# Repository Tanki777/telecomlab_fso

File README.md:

# Modulation Schemes for Free Space Optical Communication
This repository contains all GNU Radio flowgraphs, Matlab and python scripts that were used during the project. Additionally, the test data which was transmitted and received during the experiments, as well as a documentation are included.

## Table of contents
1. [GNU Radio flowgraphs](#1-gnu-radio-flowgraphs)
2. [Matlab scripts](#2-matlab-scripts)
3. [Utility scripts](#3-utility-scripts)
4. [Electrical](#4-electrical)
5. [Troubleshooting](#5-troubleshooting)

## 1. GNU Radio flowgraphs
If you are new to GNU Radio, it is recommended to have a look at the official [tutorials](https://wiki.gnuradio.org/index.php/Tutorials) first. After that, the following descriptions will be easier to understand.  
While reading the following descriptions, it is adviced to open the corresponding flowgraph image to follow the explanations.  
For this project, GNU Radio 3.10.12 was used.

### 1.1 Phase Shift Keying

#### 1.1.1 Random source transmission
This section refers to the flowgraphs ``ber_bpsk.grc``, ``ber_qpsk.grc``, ``ber_8psk.grc`` and ``ber_16psk.grc``. The diagram images can be found here: [ber_bpsk.pdf](GNU_Radio/Images/ber_bpsk.pdf), [ber_qpsk.pdf](GNU_Radio/Images/ber_qpsk.pdf), [ber_8psk.pdf](GNU_Radio/Images/ber_8psk.pdf), [ber_16psk.pdf](GNU_Radio/Images/ber_16psk.pdf).

The flowgraphs transmit a random source, which are bytes with values between 0 and 255. A random sequence of 30,000 bytes is sent and repeated while the flowgraph is running.

The transmission data is then modulated with the generic ``Constellation Modulator`` block, which can take different ``Constellation Object`` blocks as input. The ``Constellation Modulator`` also applies a Root-raised cosine filter. Since differential encoding is used, the constellation type parameter of the ``Constellation Object`` must not be set to ``QPSK`` as that prevents differential encoding and will not work. Instead, ``DQPSK`` may be selected. However, it is recommended to not use the preset types and instead set it to ``Variable Constellation`` and define symbol mapping and constellation points manually.

After that, the modulated signal is sent to the Pluto SDR (configured as the transmitter) using the ``PlutoSDR Sink`` block via USB and received at the Pluto SDR (Configured as the receiver), which sends the signal back to the computer via USB using the ``PlutoSDR Source`` block. In this project, two SDRs were used (one as transmitter, one as receiver). Thus, the IP in the Pluto blocks must be set accordingly in the ``IIO context URI`` parameter.

A ``FFT Root Raised Cosine Filter`` block is needed to match the filter at the transmitter.

In the ``Symbol Sync`` block, the symbols are synchronized. Different algorithms in the ``Timing Error Detector`` can be tested, while in our project y[n]y'[n] Maximum likelihood turned out to be the best overall.

The ``Costas Loop`` block locks the phase, making the constellation points appear as expected in the ``QT GUI Constellation Sink`` block. The ``Order`` parameter must be set according to how many constellation points are used. The exception is 16-PSK, where the order is still 8 (8 is the maximum value).

The ``Constellation Decoder`` block then decodes the complex signal to bytes.

Since differential encoding is used at the transmitter, a ``Differential Decoder`` block is required at the receiver.

The ``Map`` block remaps the symbol bytes and the order of the list must be the same as in the ``Constellation Object``.

Until now, the signal contains log~2~(p) bits per byte, where p is the number of constellation points. Therefore, it must be unpacked such that each byte contains one bit.

Finally, the data is written to the file as configured in the ``File Sink`` block.

The ``Probe Rate`` block regularly prints the bit rate to the terminal.

#### 1.1.2 General File transmission
This section refers to the flowgraphs ``pluto_bpsk_tx/rx.grc``, ``pluto_qpsk_tx/rx.grc`` and ``pluto_8psk_tx/rx.grc``. The diagram images can be found here: [pluto_bpsk_tx.pdf](GNU_Radio/Images/pluto_bpsk_tx.pdf), [pluto_bpsk_rx.pdf](GNU_Radio/Images/pluto_bpsk_rx.pdf), [pluto_qpsk_tx.pdf](GNU_Radio/Images/pluto_qpsk_tx.pdf), [pluto_qpsk_rx.pdf](GNU_Radio/Images/pluto_qpsk_rx.pdf), [pluto_8psk_tx.pdf](GNU_Radio/Images/pluto_8psk_tx.pdf), [pluto_8psk_rx.pdf](GNU_Radio/Images/pluto_8psk_rx.pdf).

These flowgraphs transmit any file, implementing the packeting inside the flowgraph. In contrast to repeated source transmission, the receiver should be turned on before the transmitter. Thus, the flowgraphs are splitted into a transmitter and receiver.  
A GNU Radio [tutorial](https://wiki.gnuradio.org/index.php?title=File_transfer_using_Packet_and_BPSK&oldid=14511)[^old_version] was used as a starting point (author: Dubbage) and modified.
The modulation scheme and the RB (Resource Blocks) used can be configured changing the value of ``txsim.RC``, to find the ``R.`` use the Wireless Waveform Generator Tool/App that in the "reference channel" dropdown shows the modulation scheme and Resource blocks used plus other info. Resource Blocks are important as they define the necessary bandwidth.

**Transmitter:**  
A HIER block ``File Source Packaged`` is used to read the file which should be transmitted and does the following (the diagram image can be found here: [hier_file_source_packaged.pdf](GNU_Radio/Images/hier_file_source_packaged.pdf)).

- It starts with an embedded python block ``EPB: File Source to Tagged Stream``, which first sends a preamble 64 times, then sends the file data in packets (each packet contains as many bytes as configured in the ``Pkt_len`` parameter of the ``File Source Packaged`` block). In front of each file data packet, the packet number is put. At the end, an end of file marker, the file name and a repeated post filler (64 times) is sent. A tag with the (new) packet length is also applied to make it a tagged stream (required by other blocks later). 
While the file data is encoded in Base64, everything else (including the packet number) is not encoded. The encoded file data packet is 4/3 as long as the decoded one, since Base64 encodes 3 Bytes into 4 Bytes.  
The **preamble** is ``&U...U]`` (50 times U), the **packet number frame** ``[000001]`` (always 6 digits, therefore a maximum of 999,999 packets are possible. This means a maximum file size of 999,999 times Pkt_len bytes. If larger files are desired, increase packet length or adjust packet number frame.), the **end of file marker** ``%UUU#EOF`` (followed by the file name), the **post filler** ``%UUU#EOF`` followed by 43 times the character ``U`` and ending with ``]``.
- After the embedded python block, a CRC32 code is also attached to each packet by the ``Stream CRC32`` block to detect errors at the receiver. The ``Mode`` parameter must be set to generate.
- Finally a header is also attached (including the access key ``11100001010110101110100010010011``) using the ``Protocol Formatter`` and ``Tagged Stream Mux`` blocks. The access key is used at the receiver for correlation.

As in random source transmission, the data is modulated by the ``Constellation Modulator`` block using a ``Constellation Object`` (which is configured depending on the number of constellation points). For more details, see the previous section.

The modulated signal is then sent to the Pluto SDR (configured as transmitter) using the ``PlutoSDR Sink`` via USB and sent to the Pluto SDR (configured as receiver).

**Receiver:**  
The received signal is sent to the computer via USB using the ``PlutoSDR Source`` block.

A ``FFT Root Raised Cosine Filter`` block is used to match the filter at the transmitter (which is inside of the ``Constellation Modulator`` block).

In the ``Symbol Sync`` block, the symbols are synchronized. Different algorithms in the ``Timing Error Detector`` can be tested, while in our project y[n]y'[n] Maximum likelihood turned out to be the best overall.

The ``Costas Loop`` block locks the phase, making the constellation points appear as expected in the ``QT GUI Constellation Sink`` block. The ``Order`` parameter must be set according to how many constellation points are used. The exception is 16-PSK, where the order is still 8 (8 is the maximum value).

The ``Constellation Decoder`` block then decodes the complex signal to bytes.

Since differential encoding is used at the transmitter, a ``Differential Decoder`` block is required at the receiver.

The ``Probe Rate`` block at this time does not print the bit rate, but the symbol rate (except for BPSK as it is the same there).

A HIER block ``File Sink Unpackaged mod_scheme`` is used to perform further actions before writing the data to a file. Since the mapping and unpacking depends on the constellation points, there is one block for each modulation scheme (the diagram images can be found here: [hier_file_sink_unpackaged_bpsk.pdf](GNU_Radio/Images/hier_file_sink_unpackaged_bpsk.pdf), [hier_file_sink_unpackaged_qpsk.pdf](GNU_Radio/Images/hier_file_sink_unpackaged_qpsk.pdf), [hier_file_sink_unpackaged_8psk.pdf](GNU_Radio/Images/hier_file_sink_unpackaged_8psk.pdf)).

- The ``Map`` block remaps the symbol bytes and the order of the list must be the same as in the ``Constellation Object`` (not needed in BPSK, since there is only 0 and 1).
- Until now, the signal contains log~2~(p) bits per byte, where p is the number of constellation points. Therefore, it must be unpacked such that each byte contains one bit (not needed in BPSK, since symbol is only 1 bit).
- The ``Correlate Access Code - Tag Stream`` block looks for the access code. If not found (with the ``Threshold`` parameter, the maximum number of wrong bits allowed can be changed), the packet will already be dropped at this point. The access code used is ``TODO``.
- The data is repacked from 1 relevant bit per byte (that is how the previous block outputs the data) to 8 relevant bits per byte (that is how the next block expects the data if ``Packed`` is true).
- The ``Stream CRC32`` is now set to ``Mode`` check. It drops packets when errors in the payload are detected.
- Finally, the data (without header and CRC32 checksum) is written to the configured file.

The ``File Sink Unpackaged mod_scheme`` block also outputs the input and output signal of the ``Correlate Access Code - Tag Stream`` block, comparing them in ``QT GUI Time Sink`` blocks. If, during transmission, there is an input signal but no output signal, the access code correlation failed and the packet is dropped. If there is no output signal visible during the entire transmission, it indicates something is wrong with the flowgraph.

#### 1.1.3 File transmission using pre-processed .bin files
This section refers to the flowgraphs ``raw_file_bpsk_tx/rx.grc`` and ``raw_file_qpsk_tx/rx.grc``. The diagram images can be found here: [raw_file_bpsk_tx.pdf](GNU_Radio/Images/raw_file_bpsk_tx.pdf), [raw_file_bpsk_rx.pdf](GNU_Radio/Images/raw_file_bpsk_rx.pdf), [raw_file_qpsk_tx.pdf](GNU_Radio/Images/raw_file_qpsk_tx.pdf), [raw_file_qpsk_rx.pdf](GNU_Radio/Images/raw_file_qpsk_rx.pdf).

### 1.2 Important notes using Pluto SDR
When testing flowgraphs and if the TX and RX SMA connectors of the SDRs are directly connected to each other with a cable, make sure to set the ``Attenuation TX1`` parameter of the ``PlutoSDR Sink`` block to **at least 20 dB** to prevent damaging the device. Only when using antennas or the laser, it can be set to 0 dB.

## 2. Matlab scripts

## 2.1 OFDM
To test the optical channel with more complex modulation schemes, a MATLAB help example (see https://it.mathworks.com/help/lte/ug/image-transmission-reception-using-lte-waveform-and-sdr.html for the original example) was adapted for the setup. This script encodes and packs an image into a radio frame. A baseband LTE signal with OFDM modulation is transmitted. The signal is then received, and the frequency offset is determined. After OFDM demodulation, a channel estimation is performed, and the payload of the received packets is recombined to form the received image.
OFDM subcarriers were modulated using 64-QAM (in the uploaded code, like in the original example), and 16-QAM. 

## 2.2 Pre-Processed Binary File Transmission
In the folder there are the Matlab codes used to create packets from the binary file generated from the image 'capra.jpg', 'transmit_packets.m', and to post-process the file after it has been received, 'read_received.m', that recreates the image. The folder 'transmitted_file' contains the packeted file, the folder 'received_files' contains the successfully received files, before post-processing.

## 3. Utility scripts

### 3.1 Post-processing for file transmission using GNU Radio flowgraph
If using one of the following flowgraphs ``pluto_bpsk_rx/tx.grc``, ``pluto_qpsk_rx/tx.grc`` or ``pluto_8psk_rx/tx.grc``, the received ``.tmp`` file must be post-processed to reconstruct the file data. For this, the script ``strip_preamble_mod.py`` can be used.  
The original script is authored by duggabe (see [here](https://wiki.gnuradio.org/index.php?title=File_transfer_using_Packet_and_BPSK&oldid=14511)) and was modified.[^old_version]

[^old_version]: Note that the GNU Radio tutorial was reworked and this link refers to the older version which was used in this project.

**Usage:**
````
python .\strip_preamble_mod.py in_file_name.tmp out_file_name.txt
````
The file extension of the output file must match that of the transmitted file.

**What it does:**
- Removes preamble.
- Looks for packet number frames.
- Decodes payload data (Base64) chunk-wise (each chunk is 4 Bytes) and writes it to the output file.
- Prints how many (and which) packet number frames were not detected.
- Compares content of detected packets with transmitted file and checks for bit errors.
- Prints packet error rate.

**Configuration:**  
Before using the script, it should be configured for the used transmission file and setting. The following should be checked and edited if necessary.
- Packet length (only if modified in the flowgraph).
- Preamble, end of file marker, post filler content (only if modified in the embedded python block in the flowgraph).
- Total number of packets for the transmitted file (is displayed in GNU Radio terminal after the transmission has ended).
- Whether the received file content should be compared with the transmitted file.
- Filename of the transmitted file (only if the received file content is compared with the transmitted file).

### 3.2 Missing number check for .txt files for file transmission using GNU Radio flowgraph
If using one of the flowgraphs listed in the previous section, the script ``txt_scanner.py`` can check which numbers are missing in the received file.

**Requirements:**
- The transmitted file contains ordered incrementing numbers (by 1), separated by commas (see ``test_file_tx.txt``).

**Usage:**

````
python .\txt_scanner.py
````

**What it does:**
- Prints how many (and which) numbers are missing in the received file.

**Configuration:**  
Before using the script, it should be configured as follows.
- Edit the name of the received file.
- Edit the list of numbers to be checked to match the transmitted file content.

# 4. Electrical
## 4.1 Electrical schematics
All the design files are available in the folder "ElectricalDesign", which is subdivided into "Version 1" and "Version 2". The first is the one used during our tests. The second is the improved version with all the problems we encountered fixed, plus some other nice features like pin names, use of rule areas, fixed voltage reference for the amplifier, but with the possibility to switch back to the DAC if needed, and monitor of the amplifier voltage directly from VBUS of INA226, while shunt voltage keeps reading the photodiode resistor voltage. Moreover pull-up resistors were added.
For the first version the 3 pins on the right of the receiver (SMA down) can't be used to set the voltage to the linear converter, if you want to do so remove first the DAC. Consider that SET pin provides a constant current, handle with care this connection! (Use a resistor) The central pin is a ground reference

## 4.2 Electrical connections
To connect the Arduino with the receiver you can simply connect grount to the lowermost pin (always SMA down), then moving up 5V, SDA, SCL as shown [here](ElectricalDesign/Version1/Pinout Receiver.png). On the Arduino side, if using an Arduino Mega 2560, use pin 20 for SDA and 21 for SCL. In case of Arduino Uno, connect SDA to A4 and SCL to A5, if using R4 version add pull-up resistors from the data lines to 5V or to 3.3V! You can connect 5V to Arduino's 5V pins and remember to always connect ground to the board and Arduino, even if using an external power supply.
Connect the SMA connector to the receiver port of your radio with a suitable cable.

To connect the transmitter use the given cable (D-SUB connectors), and connect it to the laser driver. The cable has a mark to indicate the transmitter (laser) side. If you want to use a desk power supply (only 1M OPV310!) connect the cable as described before, then add the cut cable and connector available in the box. On the wires cut there is a marking for "LS" Laser, "PD" Photodiode, and GND for Ground. Always use a multimeter in current mode to check the current that should never exceed 7mA. Connect the multimeter in series to the transmitter. DO NOT TRUST THE CURRENT READINGS OF THE POWER SUPPLY, might damage the laser and exceed the 1M cathegory.
Connect the SMA connector to the trasmitter port of the radio using a suitable connection

## 4.3 Alignment
To align the recevier you can run the program ``ADD LINK ARDUINO PROGRAM`` on the Arduino connected to the receiver while leaving only  ``INA.getShuntVoltage_uV();`` and its print not commented. Run the program and open the serial plotter, this will show the average voltage of the resistor connected to the photodiode, the more light enters the photodiode the greater the current it will let pass, the higher the voltage of the resistor will be. Start roughly aligning the transmitter and the receiver, you can help yourself with a phone camera, they usually seee in the NIR spectrum. after the rough alignment you can then check the serial plotter and try to reach the maximum value by moving both the receiver and transmitter set screws. Beware of local maxima, OPV302 has an output light concentration donut shaped, with the maximas on the outer part. Expect values around 1600uV for 6mA on the laser, with a receiver lens, and at oughly 1m, check the report for other values.
You can also calculate the current of the photodiode by dividing the voltage by 50, the resistance value of the resistor of the photodiode. with the current you could calculate the power that enters the photodiode, at 850nm you can divide the current by 0.3 to find the input power, check the datasheet for other wavelengths.

# 5. Troubleshooting

## 5.1 General

**Q:** Impossible to find DAC or ADC or setup is not successfu (error from the code).

**A:** Check that that the 2 wires of I2C are connected properly SDA->SDA SCL->SCL, check to have a ground connection between the Arduino and the receiver, in case you are using an external power supply. If this is ok then if you are using an Arduino Uno R4 you need external pullup resistors (from 2.2k to 20k connected to 5V or 3.3V). If you are using an Arduino Mega check which I2C pair you are using, there are many! If free always choose the first couple, located at pin 20 and 21. 
The schematics annotated of the first version are available [here](ElectricalDesign/Version1/Pinout Receiver.png), for the second version the pins are annotated in the silkscreen.

## 5.2 GNU Radio flowgraphs
**Q:** The signal is bad, what could be wrong?

**A:** Check if the laser is on (also the current). Check the laser alignment towards the receiver. Check the attenuation of the ``PlutoSDR Sink`` block and set it to 0 dB (**not** if TX and RX directly connected to each other via SMA cable). Check that the IP addresses of the SDRs are configured correctly in the ``PlutoSDR Sink`` and ``PlutoSDR Source`` blocks.

**Q:** The SDR is not detected by GNU Radio (terminal shows an error when running the flowgraph), what should i do?

**A:** Check the IP addresses of the SDRs in the flowgraph, but also make sure they are correct by clicking on the SDR in file explorer and opening config.txt. The ip is listed at ``ipaddr`` under ``[NETWORK]`` (you can also change the address). Also make sure that ``usb_ethernet_mode`` under ``[SYSTEM]`` is set to rndis. If that still does not help, check the computer network (on Windows via ``ipconfig`` in the terminal). If no Ethernet adapter category is listed, the RNDIS driver might need to be reinstalled by opening the device manager → right click unknown device → update driver → browse my computer → let me pick from a list → network adapters → microsoft → remote NDIS compatible device.

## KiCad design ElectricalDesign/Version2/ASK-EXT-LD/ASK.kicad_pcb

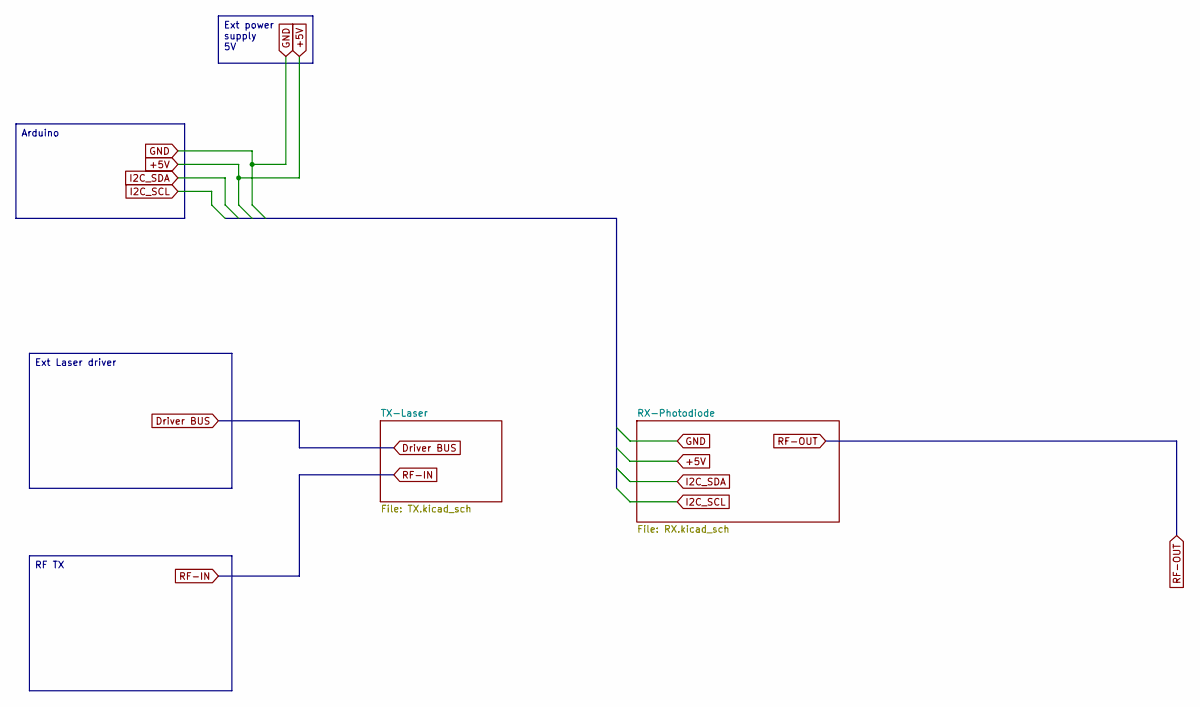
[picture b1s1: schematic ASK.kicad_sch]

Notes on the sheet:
Ext power supply 5V
Ext Laser driver
Arduino
RF TX

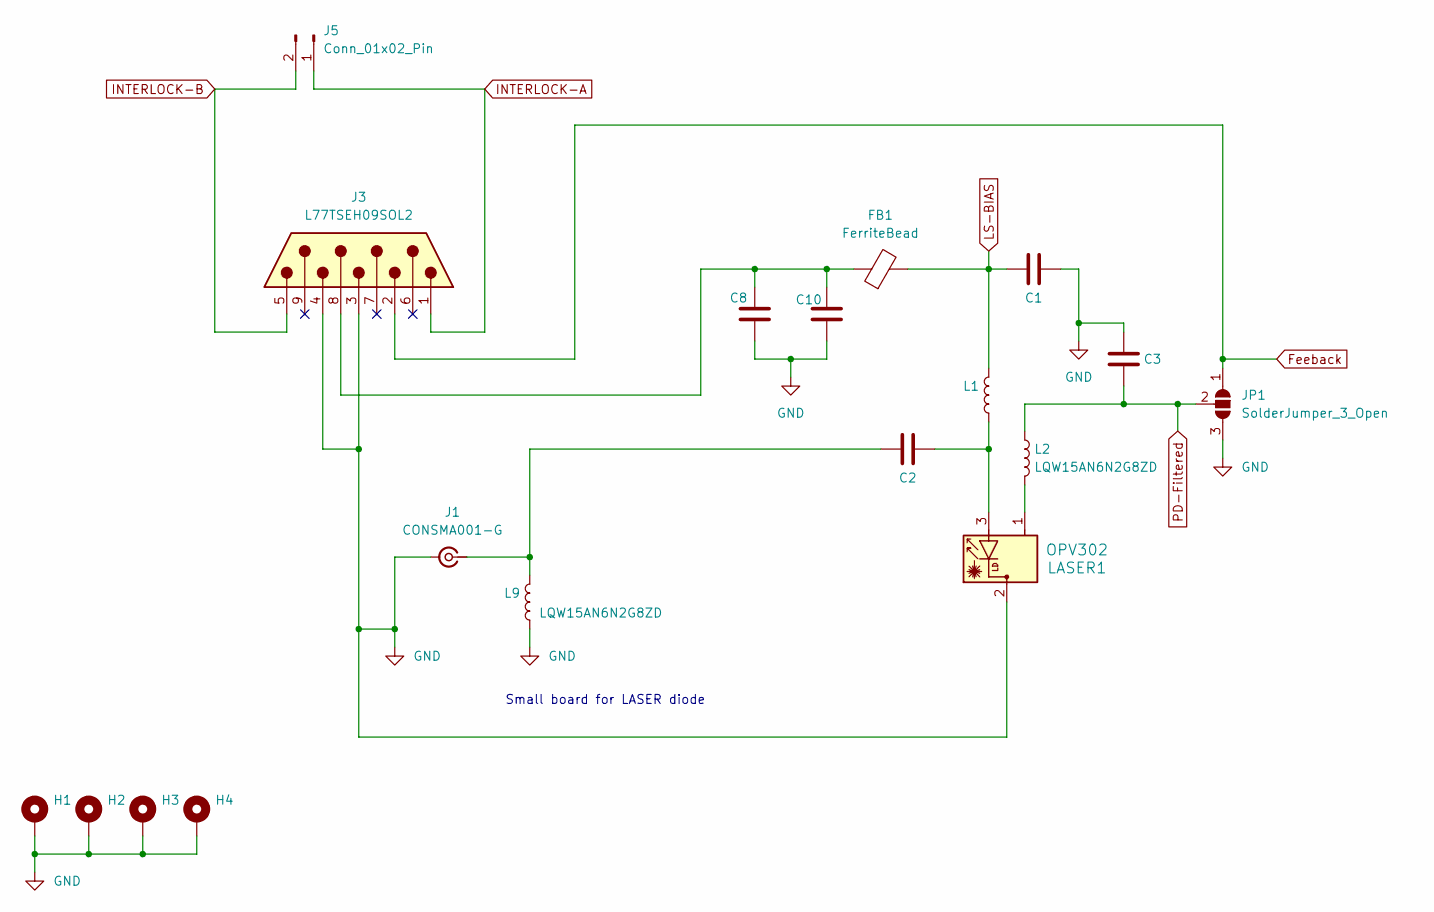
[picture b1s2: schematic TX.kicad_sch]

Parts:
C1, C3, C10: 520L103KT16; C_0402_1005Metric
C2, C8: 04025J4R0ABSTR; C_0402_1005Metric
FB1: FerriteBead; L_0402_1005Metric
H1, H2, H3, H4: MountingHole_Pad; MountingHole_2.7mm_M2.5_DIN965_Pad
J1: CONSMA001-G; CONSMA001G
J3: L77TSEH09SOL2
J5: Conn_01x02_Pin; PinHeader_1x02_P2.54mm_Vertical
JP1: SolderJumper_3_Open; SolderJumper-3_P2.0mm_Open_TrianglePad1.0x1.5mm
L1, L2, L9: LQW15AN6N2G8ZD; L_0402_1005Metric
LASER1: OPV302; OPV302_OPT

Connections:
Feeback: J3.2, JP1.1 (A)
GND: C1.2, C3.2, C8.2, C10.2, H1.1, H2.1, H3.1, H4.1, J1.2 (Ext), J1.3 (Ext), J1.4 (Ext), J1.5 (Ext), J3.3, J3.4, JP1.3 (B), L9.2, LASER1.2; also elsewhere on the board
INTERLOCK-A: J3.1, J5.1
INTERLOCK-B: J3.5, J5.2
LS-BIAS: C1.1, FB1.2, L1.1
unnamed: C2.2, L1.2, LASER1.3
unnamed: C8.1, C10.1, FB1.1, J3.8
unnamed: C2.1, J1.1 (In), L9.1
unnamed: L2.2, LASER1.1
PD-Filtered: C3.1, JP1.2 (C), L2.1

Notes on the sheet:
Small board for LASER diode

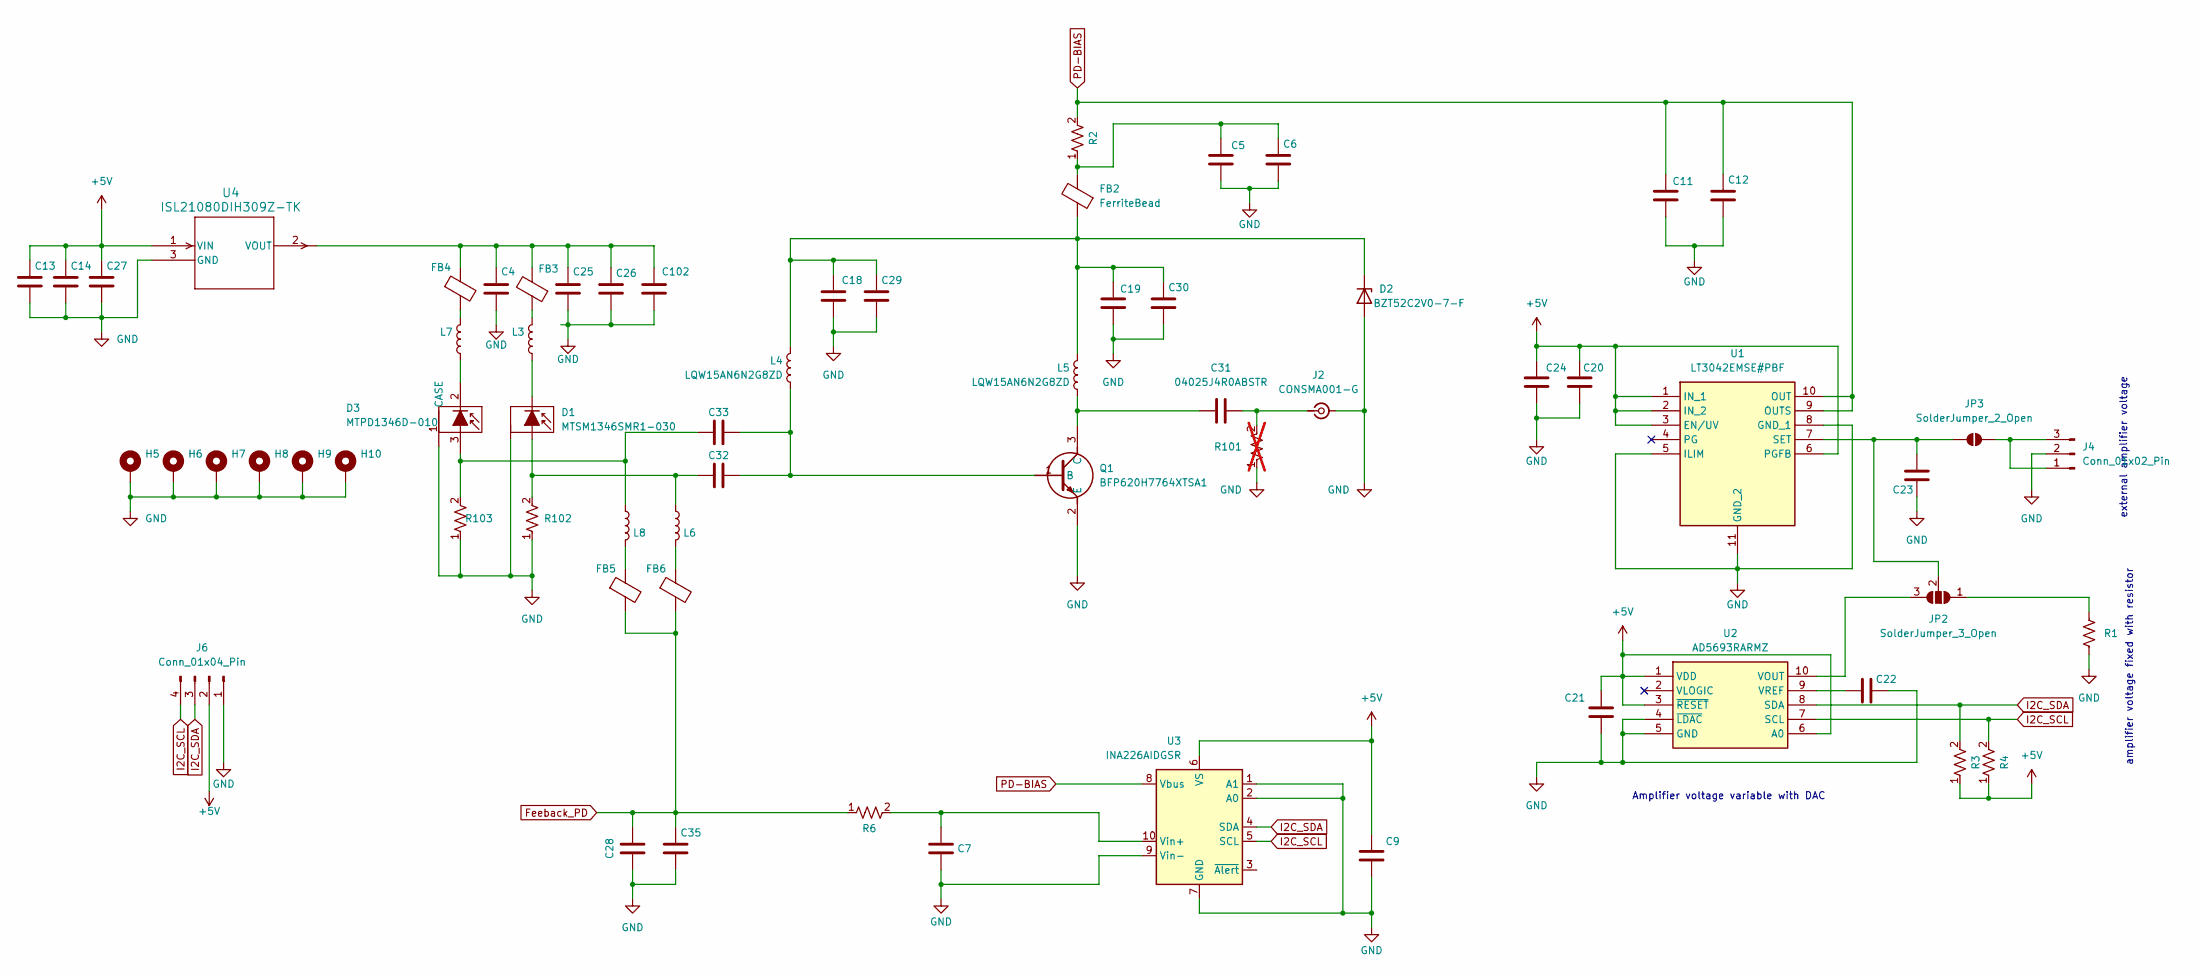
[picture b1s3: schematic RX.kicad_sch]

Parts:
C4, C24, C25: CL31B106KAHNNNE; C_0402_1005Metric
C5, C11, C18, C19, C28, C102: 520L103KT16; C_0402_1005Metric
C6, C7, C9, C12, C13, C14, C20, C21, C22, C23, C26, C27, C29, C30, C35: VJ0402Y104KXJPW1BC; C_0402_1005Metric
C31, C32, C33: 04025J4R0ABSTR; C_0402_1005Metric
D1: MTSM1346SMR1-030; SMD6_3X3_MTSM1346SMF1_MTO
D2: BZT52C2V0-7-F; D_SOD-123
D3: MTPD1346D-010; MTPD1346D010; Mouser Part Number 193-MTPD1346D-010
FB2, FB3, FB4, FB5, FB6: FerriteBead; L_0402_1005Metric
H5, H6, H7, H8, H9, H10: MountingHole_Pad; MountingHole_2.7mm_M2.5_DIN965_Pad
J2: CONSMA001-G; CONSMA001G
J4: Conn_01x02_Pin; PinHeader_1x03_P2.54mm_Vertical
J6: Conn_01x04_Pin; PinHeader_1x04_P2.54mm_Vertical
JP2: SolderJumper_3_Open; SolderJumper-3_P1.3mm_Open_RoundedPad1.0x1.5mm_NumberLabels
JP3: SolderJumper_2_Open; SolderJumper-2_P1.3mm_Open_RoundedPad1.0x1.5mm
L3, L4, L5, L6, L7, L8: LQW15AN6N2G8ZD; L_0402_1005Metric
Q1: BFP620H7764XTSA1; Mouser Part Number 726-BFP620H7764XTSA1
R1: MCS04020D1252BE100; R_0402_1005Metric
R2, R6: TNPW040210R0DEED; R_0402_1005Metric
R3, R4: ERA-2AED472X; R_0402_1005Metric
R101: FC0603E50R0BST1; R_0402_1005Metric; not fitted
R102, R103: FC0603E50R0BST1; R_0402_1005Metric
U1: LT3042EMSE#PBF; SOP50P490X110-11N; Mouser Part Number 584-LT3042EMSE#PBF
U2: AD5693RARMZ; SOP50P490X110-10N; Mouser Part Number 584-AD5693RARMZ
U3: INA226AIDGSR; VSSOP-10_3x3mm_P0.5mm
U4: ISL21080DIH309Z-TK; SOT-23-3

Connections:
+5V: C9.2, C13.1, C14.1, C20.1, C21.1, C24.1, C27.1, J6.2, R3.1, R4.1, U1.1 (IN_1), U1.2 (IN_2), U1.3 (EN/UV), U1.6 (PGFB), U2.1 (VDD), U2.3 (~RESET), U2.6 (A0), U3.6 (VS), U4.1 (VIN)
Feeback_PD: C28.1, C35.1, FB5.2, FB6.2, R6.1
GND: C4.2, C5.1, C6.2, C7.2, C9.1, C11.1, C12.2, C13.2, C14.2, C18.1, C19.1, C20.2, C21.2, C22.1, C23.1, C24.2, C25.2, C26.2, C27.2, C28.2, C29.2, C30.2, C35.2, C102.1, D1.1 (CASE), D1.3 (CASE), D1.4 (CASE), D1.6 (CASE), D2.2 (A), D3.1 (CASE), H5.1, H6.1, H7.1, H8.1, H9.1, H10.1, J2.2 (Ext), J2.3 (Ext), J2.4 (Ext), J2.5 (Ext), J4.2, J6.1, Q1.2 (E), Q1.4 (E), R1.2, R101.1, R102.1, R103.1, U1.5 (ILIM), U1.8 (GND_1), U1.11 (GND_2), U2.4 (~LDAC), U2.5 (GND), U3.1 (A1), U3.2 (A0), U3.7 (GND), U3.9 (Vin-), U4.3 (GND); also elsewhere on the board
I2C_SCL: J6.4, R4.2, U2.7 (SCL), U3.5 (SCL)
I2C_SDA: J6.3, R3.2, U2.8 (SDA), U3.4 (SDA)
unnamed: C5.2, C6.1, FB2.2, R2.1
unnamed: C32.1, D1.2 (A), L6.2, R102.2
unnamed: D1.5 (K), L3.2
unnamed: C18.2, C19.2, C29.1, C30.1, D2.1 (K), FB2.1, L4.1, L5.1
unnamed: C33.1, D3.3 (A), L8.2, R103.2
unnamed: D3.2 (K), L7.2
unnamed: FB3.1, L3.1
unnamed: FB4.2, L7.1
unnamed: FB5.1, L8.1
unnamed: FB6.1, L6.1
unnamed: C31.2, J2.1 (In), R101.2
unnamed: J4.1, J4.3, JP3.2 (B)
unnamed: JP2.1 (A), R1.1
unnamed: JP2.3 (B), U2.10 (VOUT)
unnamed: C23.2, JP2.2 (C), JP3.1 (A), U1.7 (SET)
unnamed: C32.2, C33.2, L4.2, Q1.1 (B)
unnamed: C31.1, L5.2, Q1.3 (C)
unnamed: C22.2, U2.9 (VREF)
unnamed: C7.1, R6.2, U3.10 (Vin+)
unnamed: C4.1, C25.1, C26.1, C102.2, FB3.2, FB4.1, U4.2 (VOUT)
PD-BIAS: C11.2, C12.1, R2.2, U1.9 (OUTS), U1.10 (OUT), U3.8 (Vbus)

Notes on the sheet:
amplifier voltage fixed with resistor
Amplifier voltage variable with DAC
external amplifier voltage

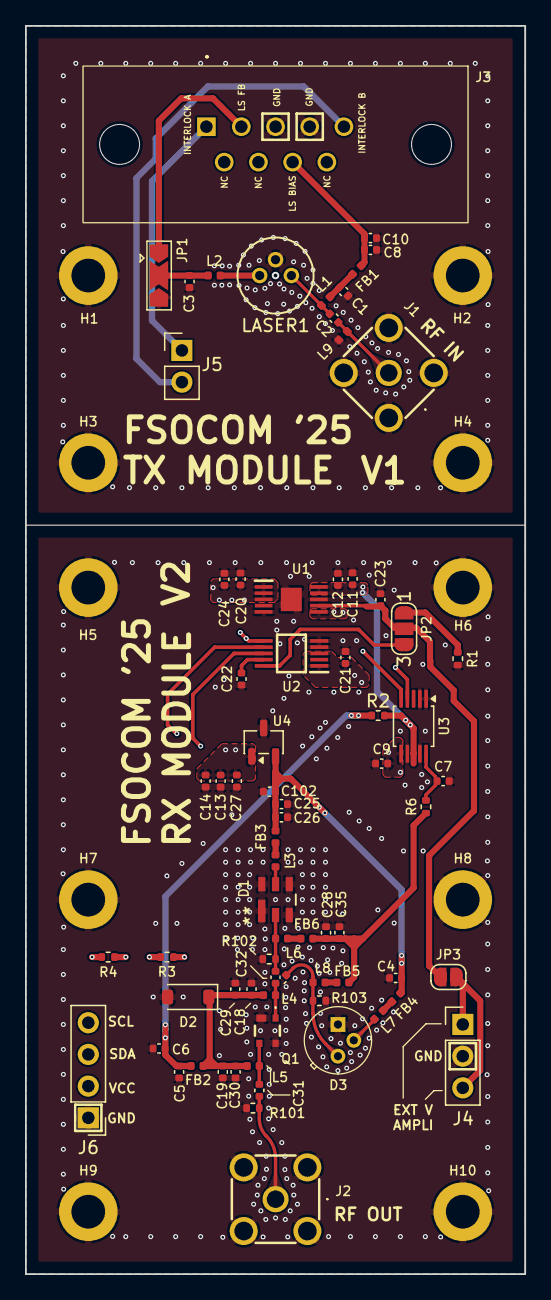
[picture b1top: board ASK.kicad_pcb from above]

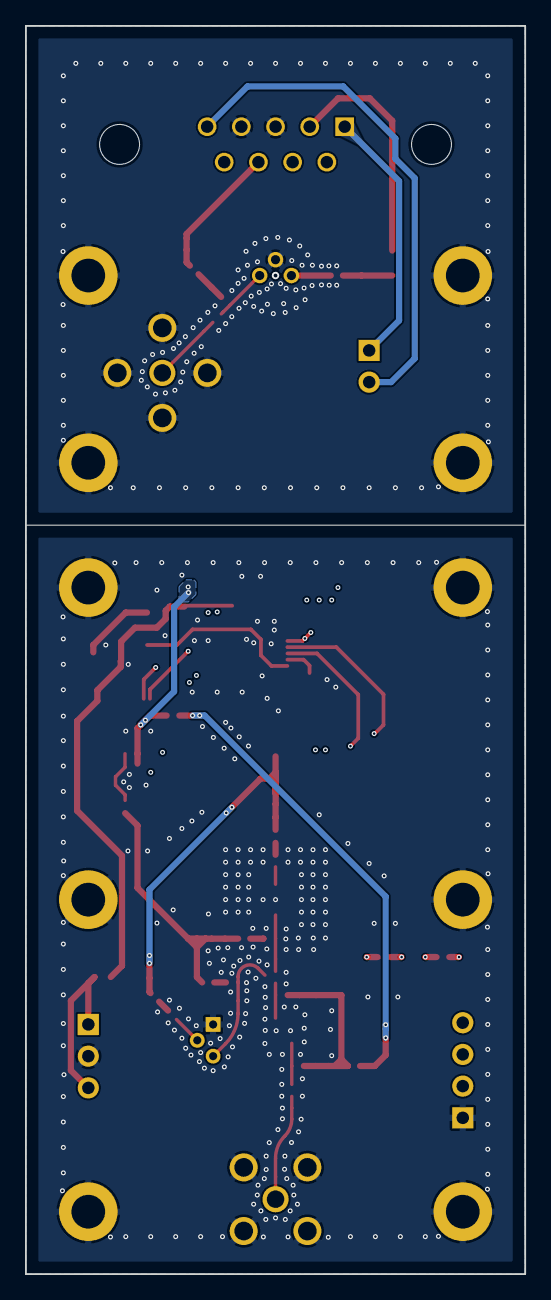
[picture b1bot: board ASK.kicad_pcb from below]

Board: 4 copper layers, 40.0 x 100.0 mm, 83 parts (3 on the bottom side), 35 nets.

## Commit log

2026-02-22 Init
2026-02-22 Added outline for README. Added content for utility scripts.
2026-02-22 Added my flowgraphs, transmitted files and utility scripts.
2026-02-22 Added license.
2026-02-22 Test footnote.
2026-02-22 Fixed footnote.
2026-02-22 Added PSK gnu radio flowgraph explanations. Added troubleshooting section.
2026-02-22 Added diagram images for gnu radio flowgraphs and reordered flowgraph source code to new folder.
2026-02-24 Added flow graph code and image for tx/rx separated and removed old versions.
2026-02-27 Added all step files of the CAD
2026-02-27 Added editable CAD drawings
2026-02-27 Create README_CAD.md with CAD design details
    Added detailed explanations for CAD files and their usage.
2026-02-27 Added files for electrical design.
2026-02-27 Added Matlab codes, preprocessed e received files
2026-02-27 Added Matlab code OFDM modulation
2026-02-28 added receiver image with annoatated pins
2026-02-28 added electrical section, added 1 general Q&A
2026-02-28 added electrical connection details on readme
    Added detailed electrical schematics and connection instructions for the receiver and transmitter, including alignment tips and troubleshooting information.
2026-02-28 Fix link casing in Electrical connections section
2026-02-28 added arduino program
2026-02-28 Added Matlab section
    Added sections for OFDM and Pre-Processed Binary File Transmission in the README.
2026-03-01 Update README with modulation scheme configuration details
    Added information about configuring modulation scheme and Resource Blocks.
2026-03-01 Fix formatting in Electrical schematics section
2026-03-01 Revise section title for Electrical connections
    Updated section titles for clarity in the README.
2026-03-01 Update link reference for Electrical section in README
2026-03-01 added spectrum analyser tests
